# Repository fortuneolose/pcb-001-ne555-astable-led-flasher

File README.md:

# PCB-001 — Adjustable NE555 Astable LED Flasher

An adjustable, through-hole NE555 astable oscillator that flashes a red LED from a 5 V supply. The project was developed progressively through analytical design, LTspice, a Tinkercad virtual breadboard, KiCad schematic capture, two-layer PCB routing, KiCad/ngspice characterization, mechanical review, and final design-rule/parity checks.

> [!IMPORTANT]
> **Current status:** the electrical design, simulations, PCB routing, 3D assembly representation, and KiCad consistency checks are complete and documented. The final PCB DRC recorded **0 violations, 0 unconnected items, 0 schematic-parity findings, and 0 ignored tests**. This is a reviewed design/simulation milestone—not a fabricated or physically validated product.

> [!NOTE]
> **Fabrication decision:** no money is being spent on board manufacture at this stage. Gerber, drill, job, checksum, purchasing, assembly, and bench-validation activities are intentionally **deferred**. No Gerber or drill package exists in this repository.

## Contents

- [Project snapshot](#project-snapshot)
- [Engineering workflow and gate status](#engineering-workflow-and-gate-status)
- [Circuit architecture](#circuit-architecture)
- [How the astable oscillator works](#how-the-astable-oscillator-works)
- [Design equations](#design-equations)
- [Progressive development record](#progressive-development-record)
- [Cross-tool verification summary](#cross-tool-verification-summary)
- [PCB implementation](#pcb-implementation)
- [Exact component baseline](#exact-component-baseline)
- [Mechanical and silkscreen review](#mechanical-and-silkscreen-review)
- [Final verification](#final-verification)
- [Repository map](#repository-map)
- [Reproducing the work](#reproducing-the-work)
- [Known limitations and remaining gates](#known-limitations-and-remaining-gates)
- [Primary records](#primary-records)

## Project snapshot

| Item | Final recorded design |
|---|---|
| Function | Adjustable NE555 astable oscillator driving a red LED |
| Supply | 5 V DC through J1; pin 1 = +5 V, pin 2 = GND |
| Timer | Texas Instruments NE555P, PDIP-8 |
| Timing network | R1 = 10 kΩ, R2 = 10 kΩ, RV1 = 100 kΩ, C1 = 10 µF |
| Timing range | Approximately 0.63 Hz to 4.8 Hz across the potentiometer range |
| LED branch | U1 OUT → D1 red LED → R3 330 Ω → GND |
| Support capacitors | C2 = 10 nF on CONT; C3 = 100 nF across the supply |
| Test access | TP1 +5 V, TP2 GND, TP3 VOUT, TP4 VCAP |
| PCB | 38.50 mm × 40.75 mm, 2 layers, through-hole, no vias |
| Copper | 0.50 mm power/GND traces; 0.30 mm signal/timing traces; GND zones on both layers |
| Final KiCad result | DRC 0; unconnected 0; parity 0; ignored tests 0 |
| Manufacturing | Intentionally deferred; no Gerbers or drills generated |

## Engineering workflow and gate status

The repository follows a gated engineering workflow. Evidence from one stage does not automatically prove the next stage.

```mermaid
flowchart LR
    A["1. Analytical design<br/>PASS"] --> B["2. LTspice sweep<br/>PASS"]
    B --> C["3. Tinkercad breadboard<br/>PASS"]
    C --> D["4. KiCad schematic<br/>ERC/parity clean"]
    D --> E["5. PCB layout<br/>DRC clean"]
    E --> F["6. Fabrication outputs<br/>DEFERRED"]
    F --> G["7. Assembly/inspection<br/>NOT PERFORMED"]
    G --> H["8. Physical validation<br/>PENDING"]

    classDef pass fill:#d9f2df,stroke:#20834f,color:#123a24;
    classDef deferred fill:#fff2cc,stroke:#b8860b,color:#5f4700;
    classDef pending fill:#eeeeee,stroke:#777,color:#333;
    class A,B,C,D,E pass;
    class F deferred;
    class G,H pending;
```

| Gate | Evidence | Status |
|---|---|---|
| Analytical design | Standard NE555 equations and MATLAB learning model | PASS in the historical project record |
| LTspice full-range verification | Three-step `RBval` sweep, saved `.asc`, `.log`, and raw results | PASS in the historical project record |
| LED output verification | LTspice LED-current measurements | PASS in the historical project record |
| Tinkercad virtual breadboard | Corrected Arduino logger plus minimum/midpoint/maximum evidence | PASS |
| KiCad schematic review | Authoritative schematic, component metadata, ERC/parity cleanup | Complete; final parity clean |
| PCB layout review | Routed two-layer board, copper zones, mechanical review, final DRC | Complete; final DRC clean |
| KiCad transient characterization | UA555 model, timing range, LED current/voltage/power exports | Evidence recorded; not a formal requirement PASS because acceptance criteria and the exact KiCad version were not recorded before the run |
| Fabrication/assembly/physical test | No board ordered or assembled | Deferred/pending |

## Circuit architecture

```mermaid
flowchart TB
    J1P["J1.1 +5 V"] --> R1["R1 10 kΩ"]
    R1 --> DIS["U1 pin 7 DISCH"]
    DIS --> R2["R2 10 kΩ"]
    R2 --> RV1["RV1 0–100 kΩ<br/>rheostat"]
    RV1 --> VCAP["VCAP timing node"]
    VCAP --> C1["C1 10 µF"]
    C1 --> GND["GND"]

    VCAP --> TRIG["U1 pin 2 TRIG"]
    VCAP --> THRES["U1 pin 6 THRES"]
    J1P --> VCC["U1 pin 8 VCC"]
    J1P --> RESET["U1 pin 4 RESET"]
    VCC --> C3["C3 100 nF"] --> GND
    CONT["U1 pin 5 CONT"] --> C2["C2 10 nF"] --> GND
    OUT["U1 pin 3 OUT / VOUT"] --> D1["D1 red LED"] --> R3["R3 330 Ω"] --> GND
    J1G["J1.2 GND"] --> GND

    TP1["TP1 +5 V"] --- J1P
    TP2["TP2 GND"] --- GND
    TP3["TP3 VOUT"] --- OUT
    TP4["TP4 VCAP"] --- VCAP
```

### NE555 pin map

| Pin | Name | Connection in PCB-001 |
|---:|---|---|
| 1 | GND | Ground plane and J1 pin 2 |
| 2 | TRIG | VCAP timing node |
| 3 | OUT | VOUT, TP3, and LED branch |
| 4 | RESET | +5 V |
| 5 | CONT | C2 10 nF to GND |
| 6 | THRES | VCAP timing node |
| 7 | DISCH | Junction of R1 and R2 |
| 8 | VCC | +5 V and local C3 decoupling |

## How the astable oscillator works

```mermaid
stateDiagram-v2
    [*] --> Charging
    Charging: OUT is HIGH
    Charging: Discharge transistor is OFF
    Charging: C1 charges through R1 + R2 + RV1
    Charging --> Discharging: VCAP reaches 2/3 VCC
    Discharging: OUT is LOW
    Discharging: Discharge transistor is ON
    Discharging: C1 discharges through R2 + RV1
    Discharging --> Charging: VCAP falls to 1/3 VCC
```

The two internal comparator thresholds are:

$$
V_{TRIG}=\frac{V_{CC}}{3}, \qquad V_{THRES}=\frac{2V_{CC}}{3}
$$

For a 5 V supply, the ideal thresholds are approximately 1.667 V and 3.333 V. The external capacitor repeatedly moves between those limits while `VOUT` toggles.

## Design equations

For the production timing network, define:

$$
R_A=R_1=10\text{ k}\Omega
$$

$$
R_B=R_2+R_{V1}
$$

$$
C=C_1=10\ \mu\text{F}
$$

The standard bipolar-555 astable approximations are:

$$
t_{HIGH}=\ln(2)(R_A+R_B)C
$$

$$
t_{LOW}=\ln(2)R_BC
$$

$$
T=t_{HIGH}+t_{LOW}=\ln(2)(R_A+2R_B)C
$$

$$
f=\frac{1}{T}
$$

$$
D=\frac{t_{HIGH}}{T}=\frac{R_A+R_B}{R_A+2R_B}
$$

The idealized production-network range is therefore:

| RV1 setting | Effective R_B | Ideal t_HIGH | Ideal t_LOW | Ideal period | Ideal frequency | Ideal duty |
|---:|---:|---:|---:|---:|---:|---:|
| 0 Ω | 10 kΩ | 0.139 s | 0.069 s | 0.208 s | 4.81 Hz | 66.7% |
| 50 kΩ | 60 kΩ | 0.485 s | 0.416 s | 0.901 s | 1.11 Hz | 53.8% |
| 100 kΩ | 110 kΩ | 0.832 s | 0.762 s | 1.594 s | 0.627 Hz | 52.2% |

The timing-capacitor trajectories are described by:

$$
V_C(t)=V_{CC}-(V_{CC}-V_{C0})e^{-t/((R_A+R_B)C)} \quad \text{(charging)}
$$

$$
V_C(t)=V_{C0}e^{-t/(R_BC)} \quad \text{(discharging)}
$$

For the loaded LED branch:

$$
I_{LED}\approx\frac{V_{OUT,H}-V_F}{R_3}
$$

Using the recorded KiCad-model values:

$$
I_{LED}\approx\frac{3.62\text{ V}-1.90\text{ V}}{330\ \Omega}=5.21\text{ mA}
$$

and:

$$
P_{R3}=I_{LED}^{2}R_3\approx(5.20\text{ mA})^2(330\ \Omega)=8.92\text{ mW}
$$

This is far below the controlled 0.25 W resistor rating in the simulation model. It is not a substitute for a physical temperature or tolerance test.

## Progressive development record

### 1. Analytical learning model

The project began with the standard NE555 astable equations and a MATLAB visualization of the charge/discharge cycle. The script animates `VCAP`, `VOUT`, the comparator thresholds, and the changing discharge state.

- Source: [`simulation/matlab/ne555_astable_cycle_animation.m`](simulation/matlab/ne555_astable_cycle_animation.m)
- Purpose: understand timing-node behaviour and establish expected waveform shape.
- Boundary: the MATLAB script is a conceptual learning model; the final production topology and simulator results remain the controlled evidence.

### 2. LTspice three-point sweep

The LTspice source swept the effective timing resistance at 10 kΩ, 60 kΩ, and 110 kΩ. The saved LTspice log reports:

| Effective R_B | Period | Frequency | t_HIGH | t_LOW | Duty | VCAP min/max | Peak LED current |
|---:|---:|---:|---:|---:|---:|---:|---:|
| 10 kΩ | 0.20835 s | 4.7995 Hz | 0.13882 s | 0.06953 s | 66.63% | 1.666/3.334 V | 9.005 mA |
| 60 kΩ | 0.90289 s | 1.1076 Hz | 0.48592 s | 0.41696 s | 53.82% | 1.666/3.334 V | 9.006 mA |
| 110 kΩ | 1.59743 s | 0.6260 Hz | 0.83311 s | 0.76432 s | 52.15% | 1.666/3.334 V | 9.006 mA |

Primary LTspice artifacts:

- [`simulation/ltspice/pcb001_ne555_astable.asc`](simulation/ltspice/pcb001_ne555_astable.asc)
- [`simulation/ltspice/pcb001_ne555_astable.log`](simulation/ltspice/pcb001_ne555_astable.log)
- saved `.raw` and operating-point evidence in the same directory.

### 3. Tinkercad virtual breadboard

The design was translated into a live virtual breadboard to verify practical pin mapping, potentiometer wiring, polarity, observability, and minimum/midpoint/maximum operation.

An Arduino Uno R3 logger sampled the virtual circuit every 10 ms for 8 s. The logger was later corrected so that only complete `RISE → FALL → RISE` cycles enter the averages; partial boundary cycles are excluded.

| Potentiometer | Complete cycles | Period | Frequency | Duty | VCAP range | Average VCC |
|---|---:|---:|---:|---:|---:|---:|
| Minimum | 37 | 207.838 ms | 4.8114 Hz | 66.567% | 1.5005–2.9912 V | 4.4900 V |
| Midpoint | 8 | 901.250 ms | 1.1096 Hz | 53.398% | 1.5005–2.9912 V | 4.4913 V |
| Maximum | 4 | 1597.500 ms | 0.6260 Hz | 51.487% | 1.5005–2.9912 V | 4.4916 V |

The corrected three-point Tinkercad record is marked PASS in [`simulation/tinkercad/docs/verification-summary.md`](simulation/tinkercad/docs/verification-summary.md).

### 4. KiCad production schematic

KiCad became the authoritative schematic and PCB source. The schematic includes power flags, the NE555 timing network, decoupling, LED branch, connector, and four test points.

Work completed during schematic cleanup included:

- confirming the LED current path and diode orientation;
- resolving footprint/symbol filters and parity warnings;
- normalizing R1, R2, and RV1 value strings between schematic and PCB;
- recording exact manufacturer, MPN, and datasheet metadata;
- linking U1 to the external `UA555` subcircuit model;
- preserving the production schematic separately from the simulation-only schematic.

### 5. UA555 simulation-model integration

KiCad did not provide a suitable bundled 555 macromodel for this workflow. The project therefore uses [`kicad/models/uA555.sub`](kicad/models/uA555.sub), with subcircuit `UA555` and direct symbol-to-model pin mapping:

```text
1=GND  2=TRIG  3=OUT  4=RESET
5=CONT 6=THRES 7=DISCH 8=VCC
```

The simulation schematic uses `R4` as a simulation-only substitute for RV1. `R4` was evaluated at 1 Ω, 50 kΩ, and 100 kΩ; it is not a fitted PCB component and is excluded from the production BOM.

### 6. PCB placement and routing

Routing was completed incrementally around the most sensitive and constrained paths:

```mermaid
flowchart TD
    A["Place U1, timing parts, connector,<br/>LED, and test points"] --> B["Route C3 local decoupling loop"]
    B --> C["Route VCAP: pins 2/6, C1, RV1, TP4"]
    C --> D["Route DISCH: pin 7, R2, RV1"]
    D --> E["Route +5 V distribution and TP1/J1"]
    E --> F["Route VOUT, TP3, D1, and R3"]
    F --> G["Add explicit GND paths and dual-layer zones"]
    G --> H["Refill zones and run DRC/parity"]
```

Critical decisions:

- **C3 loop:** U1 pin 8 to C3 pad 1 and U1 pin 1 to C3 pad 2 were kept compact and close to the DIP.
- **VCAP:** U1 pins 2 and 6, C1 positive, TP4, and RV1 were concentrated into a short timing-node region.
- **Layer crossings:** F.Cu and B.Cu traces may cross without electrical contact. Through-hole pads provide layer access, so no vias were needed.
- **Widths:** 0.50 mm was used for +5 V and explicit GND traces; 0.30 mm was used for timing and ordinary signals.
- **Ground:** GND zones were added on F.Cu and B.Cu with thermal reliefs and island removal.

### 7. KiCad timing and loaded-LED characterization

The KiCad transient runs used 5 V, PSpice/LTspice compatibility, and a 100 µs time step/maximum step. Timing-range runs excluded D1 and R3; the loaded run restored the LED branch at the 50 kΩ setting.

| R4 simulation setting | Period | Frequency | High | Low | Duty | VCAP range |
|---:|---:|---:|---:|---:|---:|---:|
| 1 Ω | 0.197 s | 5.08 Hz | 0.127 s | 0.070 s | 64.5% | about 1.85–3.38 V |
| 50 kΩ | 0.845 s | 1.18 Hz | 0.443 s | 0.402 s | 52.4% | about 1.85–3.38 V |
| 100 kΩ | 1.45 s | 0.690 Hz | 0.767 s | 0.683 s | 52.9% | about 1.85–3.38 V |

The loaded LED branch at 50 kΩ produced approximately 3.62 V VOUT high, 1.90 V LED forward drop, 5.20 mA LED current, and 8.92 mW steady R3 power. The maximum saved R3 transient power was 10.19 mW.

Every plot has a matching CSV export under [`simulation/kicad/schematic_simulation_response_plots/`](simulation/kicad/schematic_simulation_response_plots/).

### 8. Production definition, 3D models, and final audit

The project then moved from electrical completion to production-focused definition without generating manufacturing outputs:

- exact manufacturer part numbers and datasheets were recorded;
- a controlled production BOM and bare-board profile were created;
- manufacturer STEP models were assigned for Bourns RV1 and Same Sky J1;
- RV1 pin/body alignment and J1 wire-entry orientation were corrected;
- +5V/GND/VOUT/VCAP functional silkscreen labels were added;
- the completed board was visually reviewed from the front and back;
- KiCad DRC and schematic parity were rerun to a clean state.

## Cross-tool verification summary

The three major electrical models agree on the intended adjustable trend and threshold behaviour. Differences reflect model implementation, supply assumptions, measurement methods, and the generic KiCad LED/model setup.

| Setting | Ideal equation | LTspice | Tinkercad corrected logger | KiCad UA555 characterization |
|---|---:|---:|---:|---:|
| Minimum | 4.81 Hz | 4.7995 Hz | 4.8114 Hz | 5.08 Hz |
| Midpoint | 1.11 Hz | 1.1076 Hz | 1.1096 Hz | 1.18 Hz |
| Maximum | 0.627 Hz | 0.6260 Hz | 0.6260 Hz | 0.690 Hz |

```mermaid
flowchart LR
    EQ["Analytical equations"] --> CMP["Expected range and trend"]
    LT["LTspice sweep"] --> CMP
    TC["Tinkercad logger"] --> CMP
    KC["KiCad UA555 model"] --> CMP
    CMP --> PCB["Authoritative KiCad schematic + PCB"]
    PCB --> DRC["ERC / parity / DRC evidence"]
    DRC --> DEC["Reviewed design milestone<br/>fabrication deferred"]
```

## PCB implementation

### Board and copper inventory

| Property | Recorded value |
|---|---:|
| Width | 38.50 mm |
| Height | 40.75 mm |
| Copper layers | 2 |
| F.Cu +5 V segments | 11 at 0.50 mm |
| F.Cu GND segments | 2 at 0.50 mm |
| Remaining F.Cu signal segments | 18 at 0.30 mm |
| B.Cu signal segments | 7 at 0.30 mm |
| Total routed segments | 38 |
| Vias | 0 |
| Copper zones | GND on F.Cu and B.Cu |
| Zone clearance/minimum feature | 0.25 mm / 0.25 mm |

### Routing ownership by net

```mermaid
flowchart TB
    PWR["+5 V<br/>J1.1, TP1, U1.8, U1.4, R1, C3"]
    GND["GND<br/>J1.2, TP2, U1.1, C1-, C2, C3, R3"]
    VCAP["VCAP<br/>U1.2, U1.6, C1+, RV1, TP4"]
    DIS["DISCH<br/>U1.7, R1/R2 timing chain"]
    OUT["VOUT<br/>U1.3, TP3, D1/R3 branch"]

    PWR --> W50["0.50 mm explicit power traces"]
    GND --> ZONE["0.50 mm local traces + dual-layer zones"]
    VCAP --> W30["0.30 mm signal routing"]
    DIS --> W30
    OUT --> W30
```

## Exact component baseline

| References | Manufacturer | Part number | Controlled purpose |
|---|---|---|---|
| U1 | Texas Instruments | `NE555P` | Bipolar PDIP-8 timer |
| RV1 | Bourns | `3386P-1-104LF` | 100 kΩ top-adjust trimmer |
| R1, R2 | YAGEO | `MFR-25FBF52-10K` | 10 kΩ, 1%, 0.25 W axial |
| R3 | YAGEO | `MFR-25FBF52-330R` | 330 Ω, 1%, 0.25 W axial |
| C1 | Panasonic Industry | `ECEA1VKA100` | 10 µF, 35 V radial electrolytic |
| C2 | Vishay BCcomponents | `K103K10X7RF53H5` | 10 nF X7R radial MLCC |
| C3 | Vishay BCcomponents | `K104K10X7RF53H5` | 100 nF X7R radial MLCC |
| D1 | Kingbright | `L-53LID` | Low-current red 5 mm LED |
| J1 | Same Sky | `TB007-508-02BE` | 2-position 5.08 mm horizontal terminal block |

The machine-readable version is [`fabrication/PCB-001-production-bom.csv`](fabrication/PCB-001-production-bom.csv). Substitutions require electrical, dimensional, polarity, footprint, and verification review.

## Mechanical and silkscreen review

The Bourns and Same Sky manufacturer STEP models are repository-local so the final board can be rendered reproducibly:

- `kicad/pcb-001-ne555/models/Bourns_3386P001XXX.stp`
- `kicad/pcb-001-ne555/models/Same_Sky_TB007-508-02BE.step`

The first assignments exposed visible model errors: RV1 pins did not coincide with the board holes, and J1's body/wire-entry direction was wrong. Footprint-level model offsets and rotations were corrected until the pins, screws, bodies, adjustment slot, and horizontal wire access aligned with the PCB.

Functional F.Silkscreen labels were added:

| Location | Label |
|---|---|
| J1 pin 1 | +5V |
| J1 pin 2 | GND |
| TP1 | +5V |
| TP2 | GND |
| TP3 | VOUT |
| TP4 | VCAP |

Mechanical observations:

- J1 is accessible at the top/right edge; its courtyard-to-edge margin is close at roughly 0.35 mm.
- TP2 is close to the right edge at roughly 0.50 mm courtyard margin.
- RV1 remains top-adjustable from the component side.
- U1 pin 1/notch, C1 positive, D1 cathode, and J1 pin 1 are identifiable.
- No mounting holes are present; any later enclosure must account for that.

## Final verification

| KiCad check | Final count | Interpretation |
|---|---:|---|
| PCB violations | 0 | Configured design rules clean |
| Unconnected items | 0 | All intended nets routed |
| Schematic parity | 0 | Schematic/footprint/value relationship synchronized |
| Ignored tests | 0 | No current DRC exceptions |

The clean DRC is evidence for the saved design state. It does not prove manufacturability at a chosen vendor, component availability, assembly quality, or physical performance.

## Fabrication decision and deferred outputs

The component definition and fabrication profile were prepared as a future planning baseline, but the project owner decided not to spend money on fabrication now.

| Output/gate | State | Reason |
|---|---|---|
| Gerber X2 plots | Not generated | Fabrication intentionally deferred |
| Excellon drill/drill map | Not generated | Fabrication intentionally deferred |
| Gerber job/checksum archive | Not generated | No release package requested |
| Independent Gerber/drill inspection | Not performed | Requires generated outputs |
| Fabricator electrical test | Not performed | No manufacturing order |
| Assembly and visual inspection | Not performed | No physical board |
| Powered bench validation | Not performed | No physical board |
| Physical requirement closure | Pending | Simulation and DRC are not substitutes |

If fabrication is reconsidered, start from the release gates in [`fabrication/PCB-001-fabrication-profile.md`](fabrication/PCB-001-fabrication-profile.md); do not assume this repository is already a released manufacturing package.

## Repository map

```text
.
├── README.md
├── AGENTS.md
├── docs/
│   ├── images/                         # README engineering evidence
│   ├── datasheets/                     # controlled reference PDFs
│   ├── test-report.md                  # KiCad simulation record
│   └── PCB-001_KiCad_Simulation_Results_2026-08-21.docx
├── fabrication/
│   ├── PCB-001-production-bom.csv
│   └── PCB-001-fabrication-profile.md
├── kicad/
│   ├── models/uA555.sub
│   ├── evidence/
│   └── pcb-001-ne555/
│       ├── pcb-001-ne555-placement-modified.kicad_pro
│       ├── pcb-001-ne555-placement-modified.kicad_sch
│       ├── pcb-001-ne555-placement-modified.kicad_pcb
│       └── models/                      # manufacturer STEP files
├── simulation/
│   ├── matlab/                          # analytical animation
│   ├── ltspice/                         # precision sweep source/results
│   ├── tinkercad/                       # breadboard docs, logger, evidence
│   └── kicad/
│       ├── simulation_schematic/
│       ├── workbook/
│       ├── schematic_simulation_response_plots/
│       └── schematic_simulation_response_plots.zip
└── worklogs/
    ├── 2026-08-13_2113/                 # earlier engineering records
    └── 2026-08-21_1935/                 # detailed final progress report
```

## Reproducing the work

### Open the authoritative KiCad design

1. Open [`kicad/pcb-001-ne555/pcb-001-ne555-placement-modified.kicad_pro`](kicad/pcb-001-ne555/pcb-001-ne555-placement-modified.kicad_pro).
2. Review the authoritative schematic and PCB in the same directory.
3. Refill copper zones before DRC.
4. Run ERC in the Schematic Editor.
5. Run PCB DRC with schematic parity enabled.
6. Confirm `0/0/0/0` before treating the saved design as equivalent to the documented final state.

### Reproduce the KiCad simulation evidence

1. Open [`simulation/kicad/simulation_schematic/pcb-001-ne555.kicad_sch`](simulation/kicad/simulation_schematic/pcb-001-ne555.kicad_sch).
2. Confirm that U1 uses `UA555` from `kicad/models/uA555.sub` and that pins 1–8 map directly.
3. Use transient analysis with PSpice/LTspice compatibility.
4. Use 5 V, a 100 µs time step, and a 100 µs maximum step.
5. For timing characterization, exclude D1 and R3 and set R4 to 1 Ω, 50 kΩ, or 100 kΩ.
6. Use 2 s for the 1 Ω/50 kΩ cases and 10 s for the 100 kΩ case.
7. For the loaded LED case, restore D1 and R3, set R4 to 50 kΩ, use 2 s, and save voltages, currents, and power.
8. The retained simulator workbook is [`simulation/kicad/workbook/pcb-001-ne555.wbk`](simulation/kicad/workbook/pcb-001-ne555.wbk).

### Reproduce LTspice

1. Open `simulation/ltspice/pcb001_ne555_astable.asc` in LTspice.
2. Run the transient sweep.
3. Review period, frequency, duty, VCAP limits, VOUT levels, and LED current for every `RBval` step.
4. Compare against `simulation/ltspice/pcb001_ne555_astable.log` without hand-editing generated raw/log/net files.

### Reproduce the analytical visualization

With MATLAB available:

```matlab
run('simulation/matlab/ne555_astable_cycle_animation.m')
```

### Review Tinkercad evidence

The live project is cloud-hosted; reproducible repository artifacts are under `simulation/tinkercad/`. Start with:

- [`simulation/tinkercad/README.md`](simulation/tinkercad/README.md)
- [`simulation/tinkercad/docs/circuit-connections.md`](simulation/tinkercad/docs/circuit-connections.md)
- [`simulation/tinkercad/docs/verification-summary.md`](simulation/tinkercad/docs/verification-summary.md)
- [`simulation/tinkercad/arduino/pcb001_ne555_logger.ino`](simulation/tinkercad/arduino/pcb001_ne555_logger.ino)

## Known limitations and remaining gates

- The exact KiCad application version used for the final simulator/DRC runs was not recorded.
- The KiCad LED model is an adjusted generic diode (`is = 1e-18 A`, `rs = 5 Ω`, `n = 2`), not a manufacturer-specific Kingbright macromodel.
- Formal acceptance criteria were not recorded before the KiCad simulation runs, so those observations are not labelled requirement PASS results.
- No Monte Carlo/tolerance, temperature, aging, or supply-variation analysis is recorded for the final KiCad model.
- Manufacturer/model switching spikes visible in some UA555 plots are treated as numerical/model behaviour, not predicted hardware overshoot.
- No Gerber/drill outputs, independent CAM inspection, procurement check, assembly, or bench measurements exist.
- Final component values and geometry must be rechecked if any substitute part is proposed.
- The board has no mounting holes.
- A fresh ERC/DRC/parity run is required after any future metadata, schematic, footprint, routing, zone, or silkscreen change.

## Primary records

| Record | Purpose |
|---|---|
| [`docs/test-report.md`](docs/test-report.md) | KiCad simulation configuration and numeric results |
| [`docs/PCB-001_KiCad_Simulation_Results_2026-08-21.docx`](docs/PCB-001_KiCad_Simulation_Results_2026-08-21.docx) | Concise illustrated simulation report |
| [`worklogs/2026-08-21_1935/PCB-001_Engineering_Progress_Report_2026-08-21.docx`](worklogs/2026-08-21_1935/PCB-001_Engineering_Progress_Report_2026-08-21.docx) | Detailed 14-page engineering progress report |
| [`fabrication/PCB-001-production-bom.csv`](fabrication/PCB-001-production-bom.csv) | Machine-readable exact component baseline |
| [`fabrication/PCB-001-fabrication-profile.md`](fabrication/PCB-001-fabrication-profile.md) | Future board/assembly definition and release gates |
| [`simulation/tinkercad/docs/verification-summary.md`](simulation/tinkercad/docs/verification-summary.md) | Corrected virtual-breadboard verification |
| [`simulation/ltspice/pcb001_ne555_astable.log`](simulation/ltspice/pcb001_ne555_astable.log) | LTspice numerical measurement record |
| [`simulation/kicad/schematic_simulation_response_plots/`](simulation/kicad/schematic_simulation_response_plots/) | KiCad PNG and CSV evidence |

## Chronology

| Date | Milestone |
|---|---|
| 2026-08-13 to 2026-08-14 | Analytical design, LTspice, initial documentation, and Tinkercad inspection records established |
| 2026-08-15 | Corrected Arduino logger and minimum/midpoint/maximum Tinkercad dynamic verification recorded |
| 2026-08-15 to 2026-08-16 | KiCad schematic and PCB project developed; midpoint transient evidence retained |
| 2026-08-21 | Routing completion, parity/footprint cleanup, dual-layer GND zones, UA555 integration, timing and LED simulations, PNG/CSV exports, Word reports, exact BOM/fabrication profile, manufacturer 3D-model correction, silkscreen labelling, mechanical review, and final clean DRC |
| 2026-08-21 | Fabrication and Gerber generation explicitly deferred by project decision |

---

PCB-001 is retained as a complete learning, simulation, schematic, and PCB-layout milestone. Any future fabrication effort should resume at the controlled release-gate checklist rather than treating the current repository as manufacturing-released.

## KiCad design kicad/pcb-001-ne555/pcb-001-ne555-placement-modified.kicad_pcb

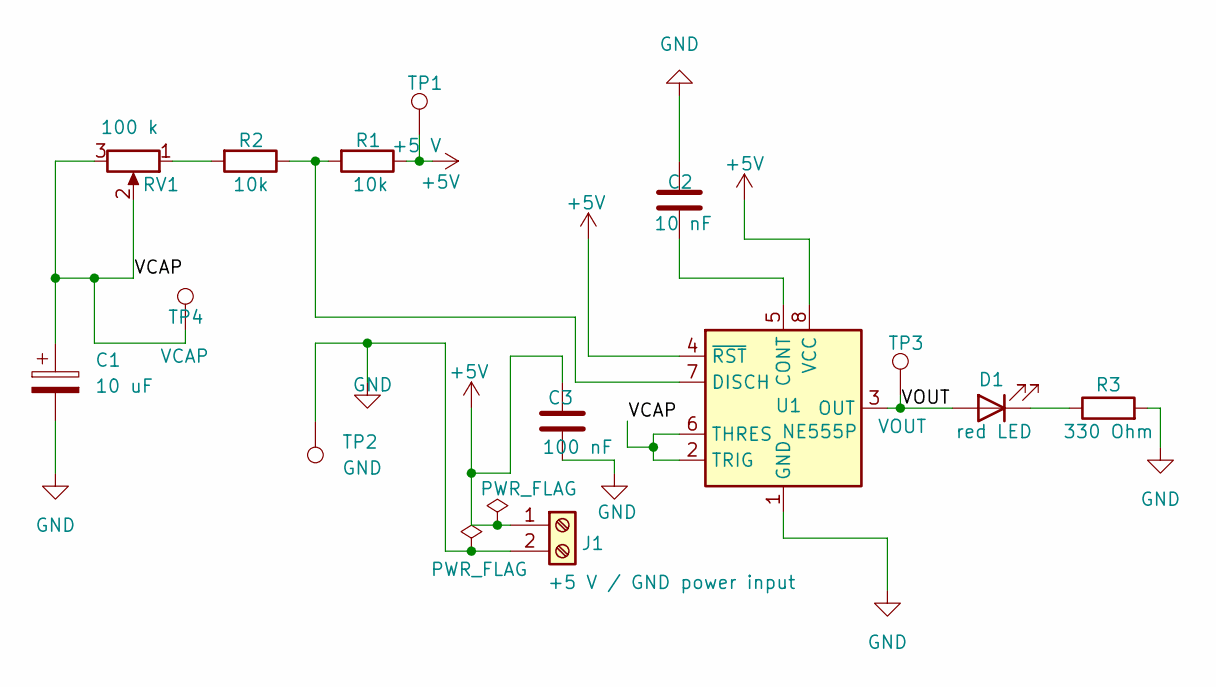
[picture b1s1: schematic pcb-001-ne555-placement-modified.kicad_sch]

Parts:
C1: 10 uF; CP_Radial_D5.0mm_P2.00mm; MPN ECEA1VKA100
C2: 10 nF; C_Disc_D5.0mm_W2.5mm_P5.00mm; MPN K103K10X7RF53H5
C3: 100 nF; C_Disc_D5.0mm_W2.5mm_P5.00mm; MPN K104K10X7RF53H5
D1: red LED; LED_D5.0mm; MPN L-53LID
J1: +5 V / GND power input; TerminalBlock_CUI_TB007-508-02_1x02_P5.08mm_Horizontal; MPN TB007-508-02BE
R1, R2: 10k; R_Axial_DIN0207_L6.3mm_D2.5mm_P10.16mm_Horizontal; MPN MFR-25FBF52-10K
R3: 330 Ohm; R_Axial_DIN0207_L6.3mm_D2.5mm_P10.16mm_Horizontal; MPN MFR-25FBF52-330R
RV1: 100 k; Potentiometer_Bourns_3386P_Vertical; MPN 3386P-1-104LF
TP1: +5 V; TestPoint_THTPad_D2.0mm_Drill1.0mm
TP2: GND; TestPoint_THTPad_D2.0mm_Drill1.0mm
TP3: VOUT; TestPoint_THTPad_D2.0mm_Drill1.0mm
TP4: VCAP; TestPoint_THTPad_D2.0mm_Drill1.0mm
U1: NE555P; DIP-8_W7.62mm; MPN NE555P

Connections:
+5V: C3.1, J1.1, R1.1, TP1.1 (1_1), U1.4 (~RST), U1.8 (VCC)
/VCAP: C1.1, RV1.2, RV1.3, TP4.1 (1_1), U1.2 (TRIG), U1.6 (THRES)
/VOUT: D1.2 (A), TP3.1 (1_1), U1.3 (OUT)
GND: C1.2, C2.1, C3.2, J1.2, R3.2, TP2.1 (1_1), U1.1 (GND)
unnamed: D1.1 (K), R3.1
unnamed: R2.2, RV1.1
unnamed: C2.2, U1.5 (CONT)
unnamed: R1.2, R2.1, U1.7 (DISCH)

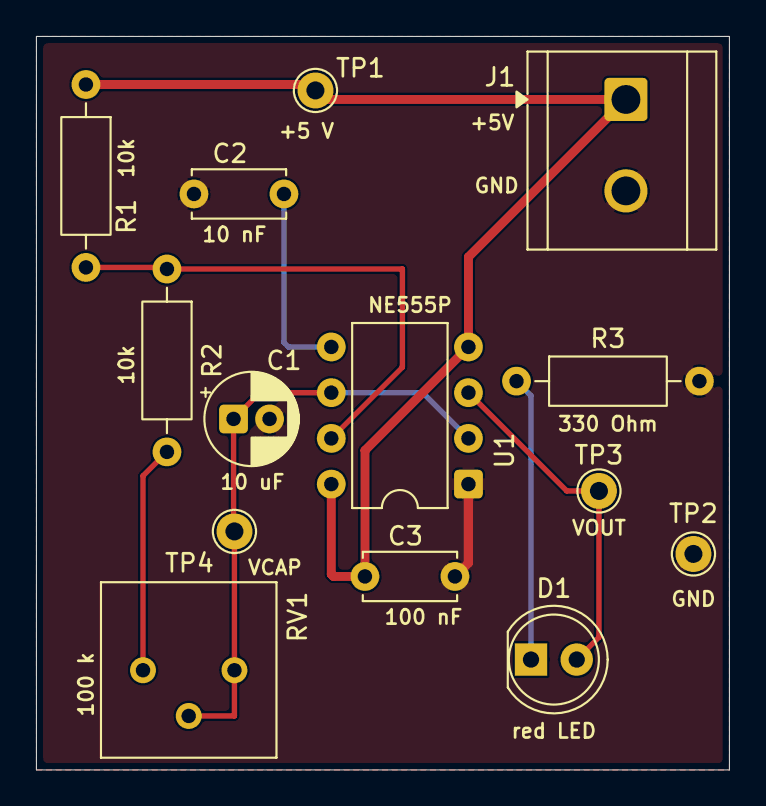
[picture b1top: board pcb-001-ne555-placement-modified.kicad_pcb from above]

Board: 2 copper layers, 38.5 x 40.8 mm, 14 parts (0 on the bottom side), 8 nets.
